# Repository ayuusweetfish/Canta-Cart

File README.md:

# Canta-Cart

Canta-Cart is a touch-operated musical instrument/synthesiser that takes the dimensions of a standard ID-1 card (85.6 × 53.98 mm). A portable little tune-maker in the pocket, it is easy for anyone to get hands on, yet versatile enough for the more aspiring of minds. It is plug-and-play — a USB-C power supply will take its sounds anywhere.

Additionally, the total BOM cost of CN¥5 / US$0.7 makes it an ideal greeting giveaway.

🎥 Videos:
- ["Merry Go Round of Life"](https://vimeo.com/989413177)
- ["A Short Hike"](https://vimeo.com/980840986)
- ["Pigeons and a Boy"](https://vimeo.com/970898009)

🕹️ [**Try in the browser**](https://ayuusweetfish.github.io/Canta-Cart/synth/)  
🌟 [Personal wiki page](https://ayu.land/canta)  
⚙️ [Hackaday project page](https://hackaday.io/project/196643-canta-cart)

## Directory Structure
- **hw/**: Circuit board design in KiCad
- **fw/**: Firmware
  - To build this, you would need a copy of the following files:
    - **debug/Puya.PY32F0xx_DFP.1.2.1.pack**: Support pack used by PyOCD for flashing and debugging. Download from [Arm Keil’s website](https://www.keil.arm.com/packs/py32f0xx_dfp-puya/versions/). (SHA-1: `d3d40536eb2b465c1fbe483f0e1d66b776cbcbb6`)
      - This can also be installed through PyOCD’s pack management system.
    - **PY32F0xx_Firmware_V1.4.1/**: Firmware library. Download from [Puya’s website](https://www.puyasemi.com/en/gongjuyuruanjian.html). (Zip SHA-1: `c5146b8456401b8718d24bd71ab4e5568bd2c0f8`)
  - And the following software (versions for reference):
    - GNU Make (3.81)
    - Arm GNU Toolchain (GCC 10.3.1)
    - PyOCD (0.36.0)
  - Run `make` to build; `make flash` to upload. Add `OPT=-O3` for an optimised build (released version).
- **misc/synth/**: The synthesiser application (emulator) and its WebGL port, both implemented with [Sokol](https://github.com/floooh/sokol)
  - **canta_synth.h**: The actual synthesiser implementation, which is also included from the firmware
- **releases/**: Gerber files submitted to fabrication houses and firmware binaries at pinned revisions

## Licence
All content in this repository is distributed under CERN-OHL-S (CERN Open Hardware Licence Version 2, Strongly Reciprocal). See full text at `COPYING.txt` or [online](https://ohwr.org/cern_ohl_s_v2.txt).

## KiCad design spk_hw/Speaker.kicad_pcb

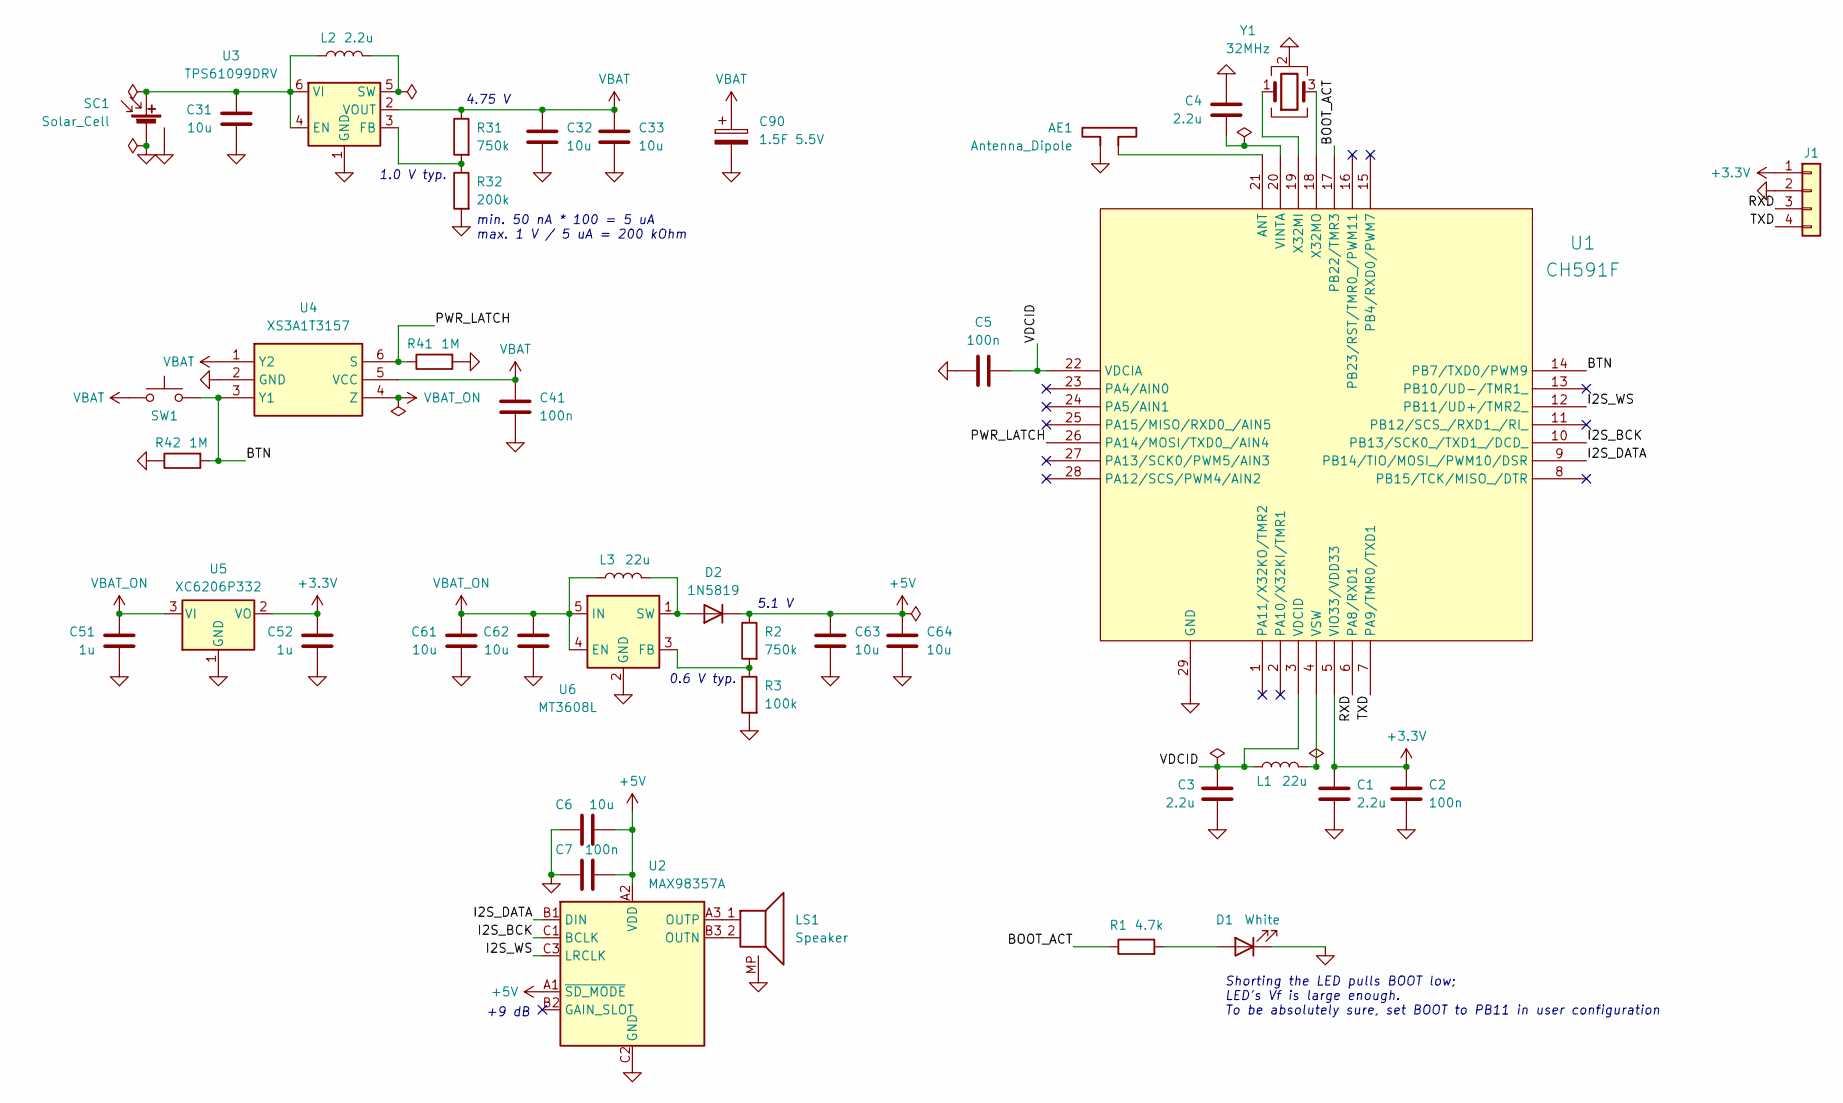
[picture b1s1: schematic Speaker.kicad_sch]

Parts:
AE1: Antenna_Dipole; ANT-F-3-2.4G-1.6mmFR4-WCH
C1, C3, C4: 2.2u; C_0402_1005Metric
C2, C5, C7, C41: 100n; C_0402_1005Metric
C6, C31, C32, C33, C61, C62, C63, C64: 10u; C_0603_1608Metric
C51, C52: 1u; C_0402_1005Metric
C90: 1.5F 5.5V; DX_5R5VxxxxU_D19.0mm_P5.00mm
D1: White; LED_0603_1608Metric
D2: 1N5819; D_SOD-323
J1: Conn_01x04; TestPoints_1x04_P2.00
L1, L3: 22u; L_Sunlord_SWPA252012S; Mfr PN SWPA252012S220MT; LCSC PN C65856
L2: 2.2u; L_Sunlord_SWPA252012S; Mfr PN SWPA252012S2R2MT; LCSC PN C23894
LS1: Speaker; JST_PH_S2B-PH-SM4-TB_1x02-1MP_P2.00mm_Horizontal
R1: 4.7k; R_0402_1005Metric
R2, R31: 750k; R_0402_1005Metric
R3: 100k; R_0402_1005Metric
R32: 200k; R_0402_1005Metric
R41, R42: 1M; R_0402_1005Metric
SC1: Solar_Cell; JST_PH_S2B-PH-SM4-TB_1x02-1MP_P2.00mm_Horizontal
SW1: SW_Push; SW_SPST_SKQG_WithStem; LCSC PN C318884
U1: CH591F; QFN-28-1EP_4x4mm_P0.4mm_EP2.7x2.7mm
U2: MAX98357A; WLCSP-9_1.21x1.22mm_Layout3x3_P0.4mm; LCSC PN C910544
U3: TPS61099DRV; WSON-6-1EP_2x2mm_P0.65mm_EP1x1.6mm; LCSC PN C2842395
U4: XS3A1T3157; XS3A1T3157GSH
U5: XC6206P332; SOT-23; LCSC PN C5446
U6: MT3608L; SOT-23-6; LCSC PN C2932326
Y1: 32MHz; Crystal_SMD_2016-4Pin_2.0x1.6mm; LCSC PN C5339095

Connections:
+3.3V: C1.1, C2.1, C52.2, J1.1, U1.5 (VIO33/VDD33), U5.2 (VO)
+5V: C6.2, C7.2, C63.2, C64.2, D2.1 (K), R2.1, U2.A1 (~SD_MODE), U2.A2 (VDD)
/BOOT_ACT: R1.1, U1.17 (PB22/TMR3)
/BTN: R42.2, SW1.2, U1.14 (PB7/TXD0/PWM9), U4.3 (Y1)
/I2S_BCK: U1.10 (PB13/SCK0_/TXD1_/DCD_), U2.C1 (BCLK)
/I2S_DATA: U1.9 (PB14/TIO/MOSI_/PWM10/DSR), U2.B1 (DIN)
/I2S_WS: U1.12 (PB11/UD+/TMR2_), U2.C3 (LRCLK)
/PWR_LATCH: R41.1, U1.26 (PA14/MOSI/TXD0_/AIN4), U4.6 (S)
/RXD: J1.3, U1.6 (PA8/RXD1)
/TXD: J1.4, U1.7 (PA9/TMR0/TXD1)
/VDCID: C3.1, C5.2, L1.1, U1.3 (VDCID), U1.22 (VDCIA)
GND: AE1.2, C1.2, C2.2, C3.2, C4.2, C5.1, C6.1, C7.1, C31.1, C32.1, C33.1, C41.1, C51.1, C52.1, C61.1, C62.1, C63.1, C64.1, C90.2, D1.1 (K), J1.2, LS1.MP, R3.2, R32.2, R41.2, R42.1, SC1.2 (-), SC1.MP, U1.29 (GND), U2.C2 (GND), U3.1 (GND), U3.7 (GND), U4.2 (GND), U5.1 (GND), U6.2 (GND), Y1.2 (G), Y1.4 (G)
unnamed: D1.2 (A), R1.2
unnamed: D2.2 (A), L3.2, U6.1 (SW)
unnamed: C31.2, L2.1, SC1.1 (+), U3.4 (EN), U3.6 (VI)
unnamed: AE1.1, U1.21 (ANT)
unnamed: C4.1, U1.20 (VINTA)
unnamed: L1.2, U1.4 (VSW)
unnamed: U1.19 (X32MI), Y1.1
unnamed: U1.18 (X32MO), Y1.3
unnamed: LS1.2, U2.B3 (OUTN)
unnamed: LS1.1, U2.A3 (OUTP)
unnamed: R31.2, R32.1, U3.3 (FB)
unnamed: L2.2, U3.5 (SW)
unnamed: R2.2, R3.1, U6.3 (FB)
VBAT: C32.2, C33.2, C41.2, C90.1, R31.1, SW1.1, U3.2 (VOUT), U4.1 (Y2), U4.5 (VCC)
VBAT_ON: C51.2, C61.2, C62.2, L3.1, U4.4 (Z), U5.3 (VI), U6.4 (EN), U6.5 (IN)

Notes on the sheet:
Shorting the LED pulls BOOT low; LED's Vf is large enough. To be absolutely sure, set BOOT to PB11 in user configuration
+9 dB
5.1 V
4.75 V
min. 50 nA * 100 = 5 uA max. 1 V / 5 uA = 200 kOhm
1.0 V typ.
0.6 V typ.

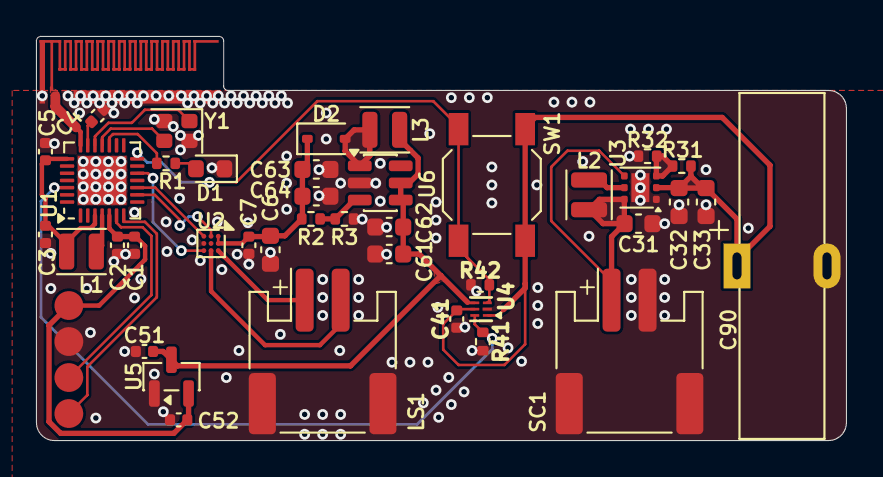
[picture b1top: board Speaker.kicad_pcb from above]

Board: 2 copper layers, 45.0 x 22.5 mm, 42 parts (0 on the bottom side), 27 nets.

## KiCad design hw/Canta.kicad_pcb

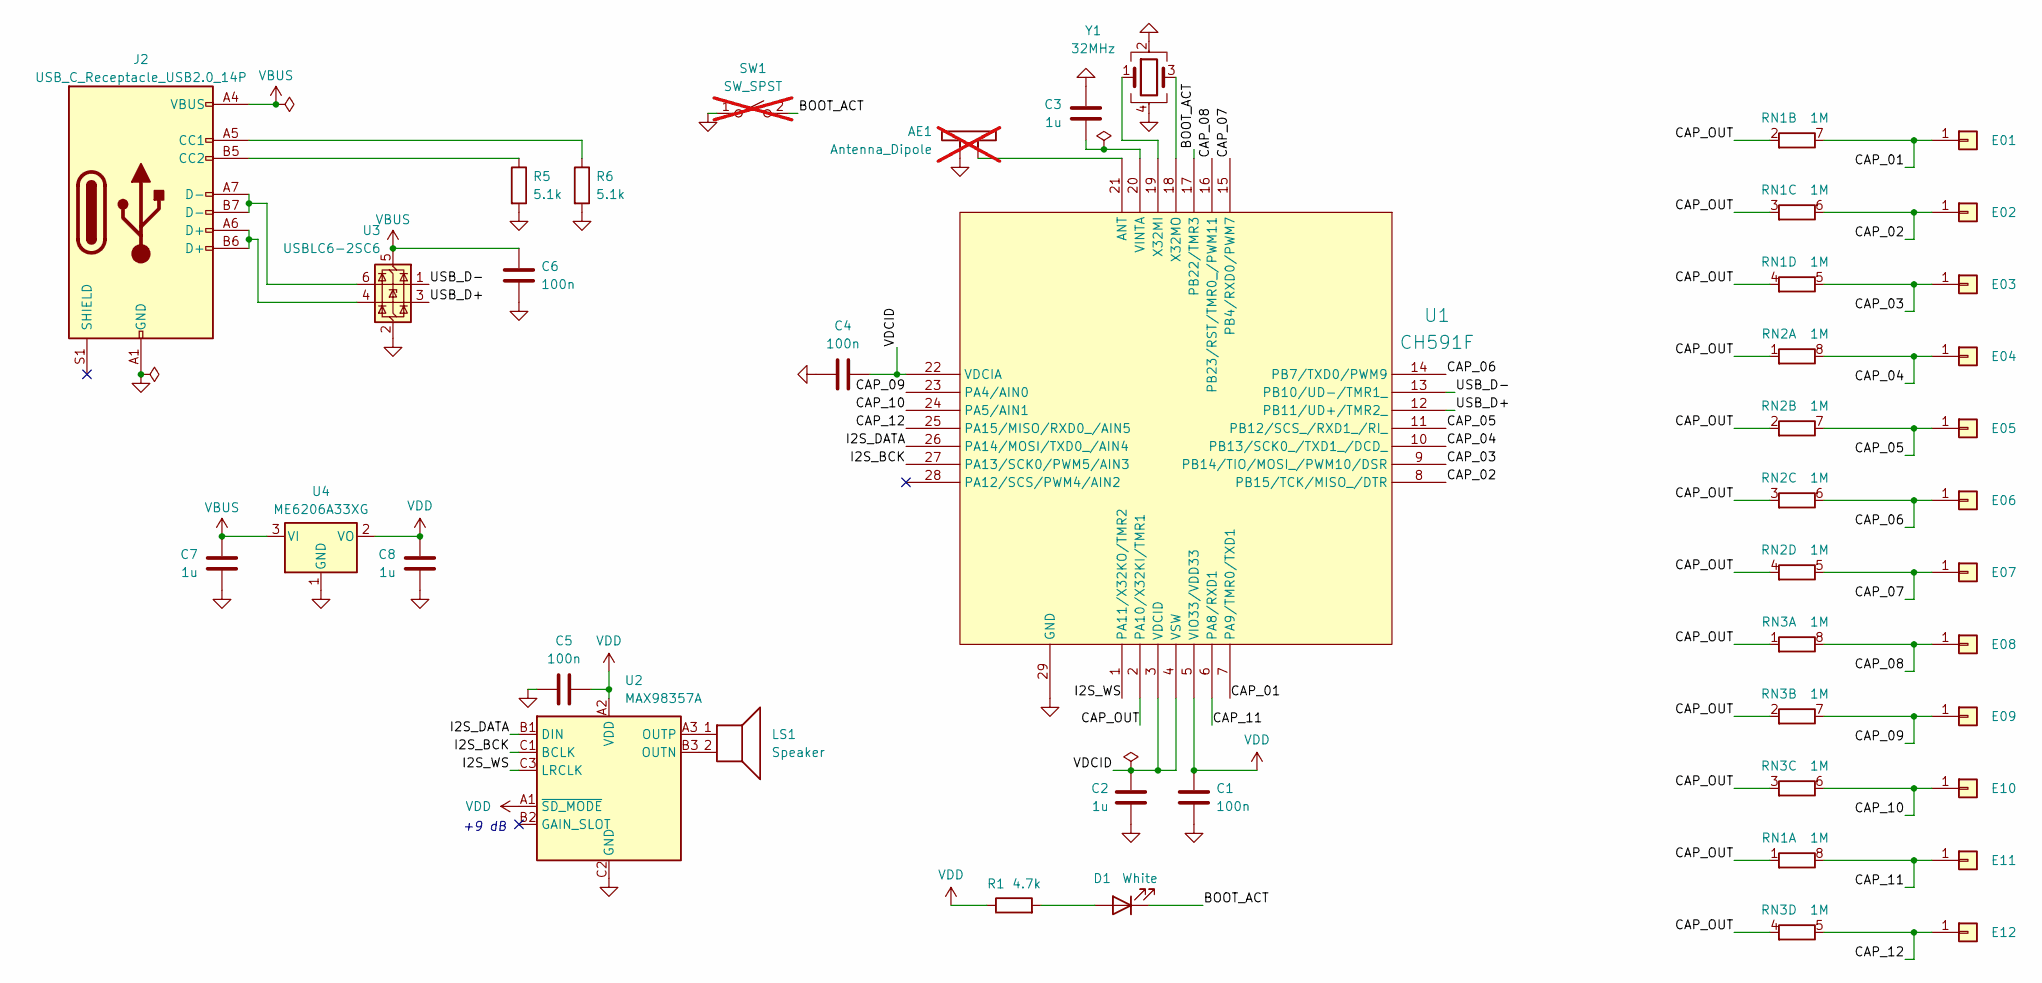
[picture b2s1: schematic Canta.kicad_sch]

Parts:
AE1: Antenna_Dipole; ANT-F-3-2.4G-1.6mmFR4-WCH; not fitted
C1, C4, C5, C6: 100n; C_0402_1005Metric
C2, C3, C7, C8: 1u; C_0402_1005Metric
D1: White; LED_0603_1608Metric
E01, E02, E03, E04, E05, E06, E07, E08, E09, E10: Conn_01x01; TouchPad_Keyboard
E11, E12: Conn_01x01; TouchPad_Transpose
J2: USB_C_Receptacle_USB2.0_14P; USB_C_Receptacle_HRO_TYPE-C-31-M-12; LCSC PN C165948
LS1: Speaker; Speaker_Pads_P2.00
R1: 4.7k; R_0402_1005Metric
R5, R6: 5.1k; R_0402_1005Metric
RN1, RN2, RN3: 1M; R_Array_Convex_4x0402
SW1: SW_SPST; TestPoints_1x02_P1.50; not fitted
U1: CH591F; QFN-28-1EP_4x4mm_P0.4mm_EP2.7x2.7mm
U2: MAX98357A; WLCSP-9_1.21x1.22mm_Layout3x3_P0.4mm; LCSC PN C910544
U3: USBLC6-2SC6; SOT-23-6
U4: ME6206A33XG; SOT-23
Y1: 32MHz; Crystal_SMD_2016-4Pin_2.0x1.6mm; LCSC PN C5339095

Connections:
/BOOT_ACT: D1.1 (K), SW1.2 (B), U1.17 (PB22/TMR3)
/CAP_01: E01.1, RN1.7 (R2.2), U1.7 (PA9/TMR0/TXD1)
/CAP_02: E02.1, RN1.6 (R3.2), U1.8 (PB15/TCK/MISO_/DTR)
/CAP_03: E03.1, RN1.5 (R4.2), U1.9 (PB14/TIO/MOSI_/PWM10/DSR)
/CAP_04: E04.1, RN2.8 (R1.2), U1.10 (PB13/SCK0_/TXD1_/DCD_)
/CAP_05: E05.1, RN2.7 (R2.2), U1.11 (PB12/SCS_/RXD1_/RI_)
/CAP_06: E06.1, RN2.6 (R3.2), U1.14 (PB7/TXD0/PWM9)
/CAP_07: E07.1, RN2.5 (R4.2), U1.15 (PB4/RXD0/PWM7)
/CAP_08: E08.1, RN3.8 (R1.2), U1.16 (PB23/RST/TMR0_/PWM11)
/CAP_09: E09.1, RN3.7 (R2.2), U1.23 (PA4/AIN0)
/CAP_10: E10.1, RN3.6 (R3.2), U1.24 (PA5/AIN1)
/CAP_11: E11.1, RN1.8 (R1.2), U1.6 (PA8/RXD1)
/CAP_12: E12.1, RN3.5 (R4.2), U1.25 (PA15/MISO/RXD0_/AIN5)
/CAP_OUT: RN1.1 (R1.1), RN1.2 (R2.1), RN1.3 (R3.1), RN1.4 (R4.1), RN2.1 (R1.1), RN2.2 (R2.1), RN2.3 (R3.1), RN2.4 (R4.1), RN3.1 (R1.1), RN3.2 (R2.1), RN3.3 (R3.1), RN3.4 (R4.1), U1.2 (PA10/X32KI/TMR1)
/I2S_BCK: U1.27 (PA13/SCK0/PWM5/AIN3), U2.C1 (BCLK)
/I2S_DATA: U1.26 (PA14/MOSI/TXD0_/AIN4), U2.B1 (DIN)
/I2S_WS: U1.1 (PA11/X32KO/TMR2), U2.C3 (LRCLK)
/USB_D+: U1.12 (PB11/UD+/TMR2_), U3.3 (I/O2)
/USB_D-: U1.13 (PB10/UD-/TMR1_), U3.1 (I/O1)
/VDCID: C2.1, C4.2, U1.3 (VDCID), U1.4 (VSW), U1.22 (VDCIA)
GND: AE1.2, C1.2, C2.2, C3.2, C4.1, C5.1, C6.2, C7.1, C8.1, J2.A1 (GND), J2.A12 (GND), J2.B1 (GND), J2.B12 (GND), R5.2, R6.2, SW1.1 (A), U1.29 (GND), U2.C2 (GND), U3.2 (GND), U4.1 (GND), Y1.2, Y1.4
unnamed: D1.2 (A), R1.2
unnamed: J2.A5 (CC1), R6.1
unnamed: J2.B5 (CC2), R5.1
unnamed: J2.A6 (D+), J2.B6 (D+), U3.4 (I/O2)
unnamed: J2.A7 (D-), J2.B7 (D-), U3.6 (I/O1)
unnamed: AE1.1, U1.21 (ANT)
unnamed: C3.1, U1.20 (VINTA)
unnamed: U1.19 (X32MI), Y1.1
unnamed: U1.18 (X32MO), Y1.3
unnamed: LS1.2, U2.B3 (OUTN)
unnamed: LS1.1, U2.A3 (OUTP)
VBUS: C6.1, C7.2, J2.A4 (VBUS), J2.A9 (VBUS), J2.B4 (VBUS), J2.B9 (VBUS), U3.5 (VBUS), U4.3 (VI)
VDD: C1.1, C5.2, C8.2, R1.1, U1.5 (VIO33/VDD33), U2.A1 (~SD_MODE), U2.A2 (VDD), U4.2 (VO)

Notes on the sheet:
+9 dB

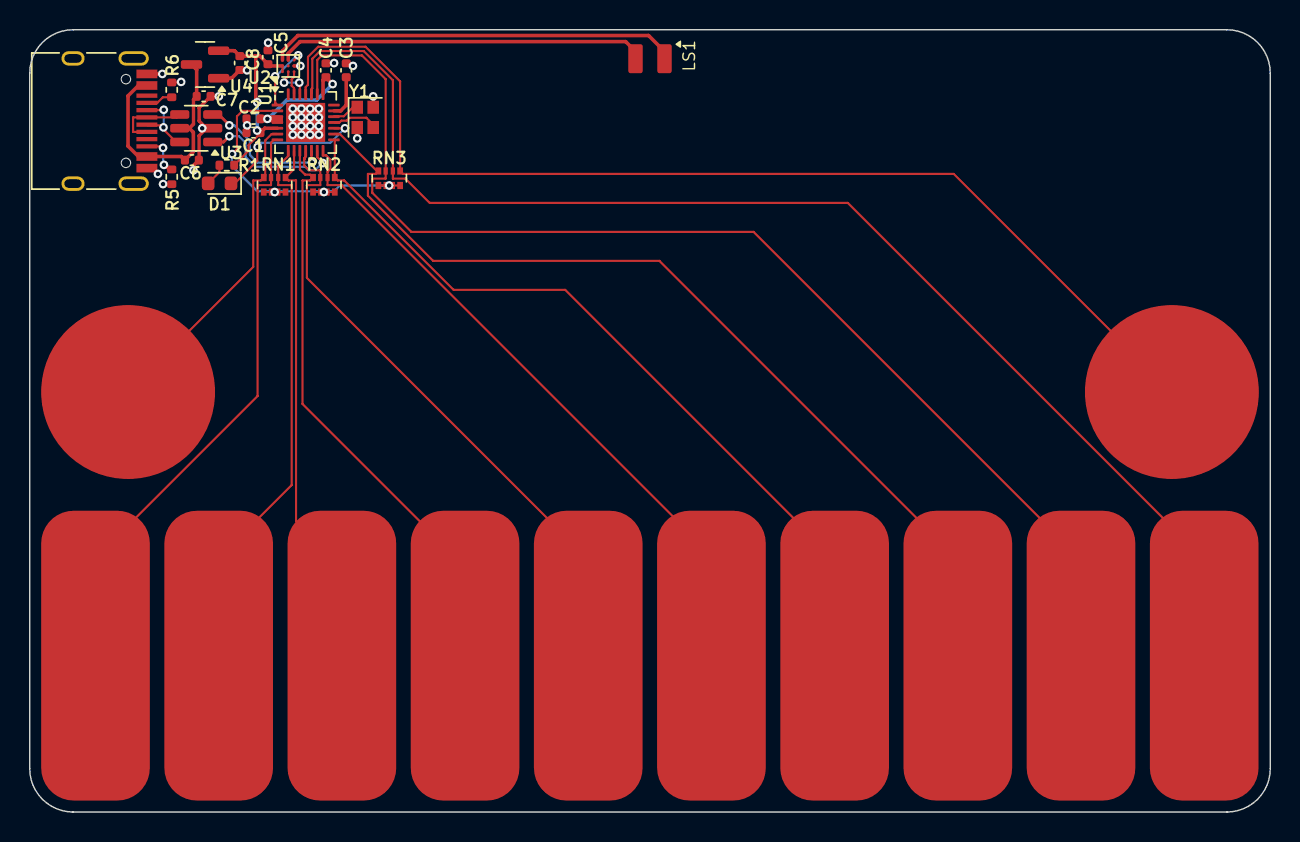
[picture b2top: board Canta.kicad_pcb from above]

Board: 2 copper layers, 85.6 x 54.0 mm, 34 parts (0 on the bottom side), 33 nets.

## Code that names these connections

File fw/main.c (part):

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
  // read vector = (A << 1) | B
  static const uint32_t MASK[12] = {
    1 << 10,  // PA9
    1 << 15,
    1 << 14,
    1 << 13,
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    1 <<  7,
    1 <<  4,
    1 << 23,
    1 <<  5,  // PA4
    1 <<  6,  // PA5
    1 <<  9,  // PA8
    1 << 16,  // PA15
  };
  static const uint32_t FULL_MASK =
    MASK[ 0] | MASK[ 1] | MASK[ 2] | MASK[ 3] | MASK[ 4] | MASK[ 5] |
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  // ============ Audio ============ //

#if !REROUTE_SIGNALS
  // WS: PA11 TMR2
  GPIOA_ResetBits(GPIO_Pin_11);
  GPIOA_ModeCfg(GPIO_Pin_11, GPIO_ModeOut_PP_5mA);
  GPIOPinRemap(DISABLE, RB_PIN_TMR2);
#else
  // WS: PB23 TMR0_ (CAP_08)
  GPIOB_ResetBits(GPIO_Pin_23);
  GPIOB_ModeCfg(GPIO_Pin_23, GPIO_ModeOut_PP_5mA);
  GPIOPinRemap(ENABLE, RB_PIN_TMR0);
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
  // Data output by SPI
#if !REROUTE_SIGNALS
  // BCK: PA13 SCK0
  // DATA: PA14 MOSI
  GPIOA_ResetBits(GPIO_Pin_13 | GPIO_Pin_14);
  GPIOA_ModeCfg(GPIO_Pin_13 | GPIO_Pin_14, GPIO_ModeOut_PP_5mA);
  GPIOPinRemap(DISABLE, RB_PIN_SPI0);
#else
  // BCK: PB13 SCK0_ (CAP_04)
  // DATA: PB14 MOSI_ (CAP_03)
  GPIOB_ResetBits(GPIO_Pin_13 | GPIO_Pin_14);
  GPIOB_ModeCfg(GPIO_Pin_13 | GPIO_Pin_14, GPIO_ModeOut_PP_5mA);
  GPIOPinRemap(ENABLE, RB_PIN_SPI0);
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  GPIOB_ModeCfg(GPIO_Pin_All, GPIO_ModeIN_Floating);

#if DEBUG
  // Debug usage. Monitor serial output at PA9 = TXD1 = bottom-left touch pad
  GPIOA_SetBits(GPIO_Pin_9);
  // GPIOA_ModeCfg(GPIO_Pin_8, GPIO_ModeIN_PU); // Probably no need
  GPIOA_ModeCfg(GPIO_Pin_9, GPIO_ModeOut_PP_5mA);
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
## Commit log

2024-06-18 🎉 Initial commit, prepare symbols and footprints
2024-06-19 Finish schematic
2024-06-19 Fix thermal pad connection in PY32 symbol
2024-06-19 Layout, I think
2024-06-19 Routing, I think
2024-06-19 Switch supplies of audio ICs to 5 V
2024-06-19 Modify entire circuit to run on 5 V
2024-06-20 Update silkscreen
2024-06-20 Add back-side image
2024-06-20 Finalise and submit for fab (Rev. 1)
2024-06-20 Add Sokol-based application template
2024-06-20 Triangle wave synthesiser
2024-06-21 Display buttons
2024-06-21 🎶 Actually making melodies!
2024-06-21 Implement attack/release envelope
2024-06-21 Implement transposition
2024-06-21 Optimise synthesiser
2024-06-21 Fix incorrect wavetable
2024-06-21 Support key change
2024-06-21 Fix popping noise during attack
2024-06-21 Display silkscreen image
2024-06-22 Compile to WebAssembly
2024-06-22 Implement interaction with pointer devices
2024-06-22 Fix touch-end event glitches
2024-06-22 ✨ Firmware?!
2024-06-22 Condense emulator to a single source file
2024-06-22 Built web synth from 382ccb8
2024-06-22 Adjust synthesiser volume
2024-06-22 Built web synth from 1f06b09
2024-06-23 Add help information on web page
2024-06-23 Update web page from 1fd798a
2024-06-24 Add missing 3D models
2024-06-24 Remove paste on touch keys
2024-06-24 Correct path in debug configuration
2024-06-24 Running with messages echoed to GDB!
2024-06-24 Minor improvements to debugging
2024-06-25 Enable HSE oscillator
2024-06-25 Dump readings
2024-06-25 Correct keypress detection
2024-06-25 🚧 Non-working audio
2024-06-25 Working sound, at least
2024-06-25 Sounding OoO
2024-06-25 Sound at touch
2024-06-25 Critical sections (untested)
2024-06-26 Eliminate on-the-fly floating-point ops in frequency calculation
2024-06-26 🎶Melodies!
2024-06-26 🚧 Timing?
2024-06-26 🚧 Strip down SPI DMA
2024-06-26 Further strip down SPI/DMA driver subroutine
2024-06-26 Switch synthesiser to stereo with correct frequencies
2024-06-27 More robust timing...?
2024-06-27 Activate all keys!
2024-06-27 Improve touch sensing with hysteresis
2024-06-27 Add sine wave wavetable
2024-06-27 Adapt touch sense threshold to different sense resistor values
2024-06-28 Fix timing issues altogether (hopefully)
2024-06-28 Update component values with actual assembly
2024-06-28 Don't want to deal with timing issues further
2024-06-28 Increase volume
2024-07-04 Add test option to ignore shorted keys…
2024-07-04 Revise hardware design
2024-07-04 Revise pin assignment; submit for fab (Rev. 2)
2024-07-10 🚧 Prepare firmware for Rev. 2 (unfinished)
2024-07-11 Fix touch sensing bitmasks
2024-07-11 Reduce duplication in touch sensing subroutine
2024-07-11 🚧 Bit clock?
2024-07-11 Properly working Rev. 2
2024-07-16 Volume readjustment & minor debug aids in firmware
2024-07-18 Improve signal timings
2024-07-18 Perfect timings with less registers and cycles?
2024-07-18 Turn off debugging aids
2024-07-18 Improve algorithm to eliminate false triggers & missed presses
2024-07-18 Build with -O3 flag
2024-07-18 Finalise firmware
2024-07-24 Upgrade PY32F0xx CMSIS pack to 1.2.1
2024-07-24 🎉 Add documentation
2024-07-24 Revise documentation
2024-08-01 Optimise sensing algorithm with conformal coating
2024-08-01 Tidy up firmware source
2024-08-01 Optimise time spent in sensing routine
2024-08-02 Refactor pin pulling subroutines
2024-08-02 Further tune sensitivity
2024-08-03 Update firmware binary
2024-08-05 Add UID inspection command
2024-08-08 Add knob model
2024-08-18 Document image header file generation (by `xxd -i`)
2024-08-30 Add PY32F003x4 compatibility
2024-09-02 Rebuild firmware, defaulting MCU model to F003x4
2024-09-02 WFI during waits
2024-09-26 Add footprint for the new potentiometer model
2025-07-03 hw: Initial project setup with libraries
2025-07-04 hw: More components in schematic
2025-07-07 hw: Add missing libraries and (mostly) finish schematic
2025-07-07 hw: Layout?
2025-07-07 hw: Layout...?
2025-07-07 hw: Some routing
2025-07-08 hw: ... > <
2025-07-09 hw: Almost done routing!
2025-07-09 hw: Submit for fab (Rev. 3)
2025-07-22 fw: Build blinking firmware for CH57x
2025-07-22 misc: Add .gitignore
2025-08-02 fw: Successfully upload with ch32-rs/wchisp
2025-08-02 fw: Switch to CH59x template library
2025-08-02 fw: Port previous capacitive sensing implementation
2025-08-02 fw: Port I2S from Plushies CH57x (WIP)
2025-08-02 fw: Switch to fast interrupt (WIP)
2025-08-03 fw: (Debug) Switch I2S output pins for probing
2025-08-03 fw: Revert pins change (still doesn't work?)
2025-08-06 fw: Tidy up debug-use I2S signal rerouting logic
2025-08-06 fw: Correctly output sine wave
2025-08-06 fw: Bring the synth back again!
2025-08-06 fw: Clean up
2025-08-06 fw: Re-enable touch pads when not debugging
2026-03-20 spk_hw: Initialize with Canta-Cart@cc
2026-03-20 spk_hw: Add DC-DC (Migration@tangibles)
2026-03-22 spk_hw: Finish schematic, finally >-<
2026-03-22 spk_hw: Board layout and routing
2026-03-24 spk_hw: Add many vias
2026-03-24 spk_hw: Sign off
2026-03-24 spk_hw: Increase BGA pad size due to fabricator constraints >_<
2026-05-22 Update personal site link
